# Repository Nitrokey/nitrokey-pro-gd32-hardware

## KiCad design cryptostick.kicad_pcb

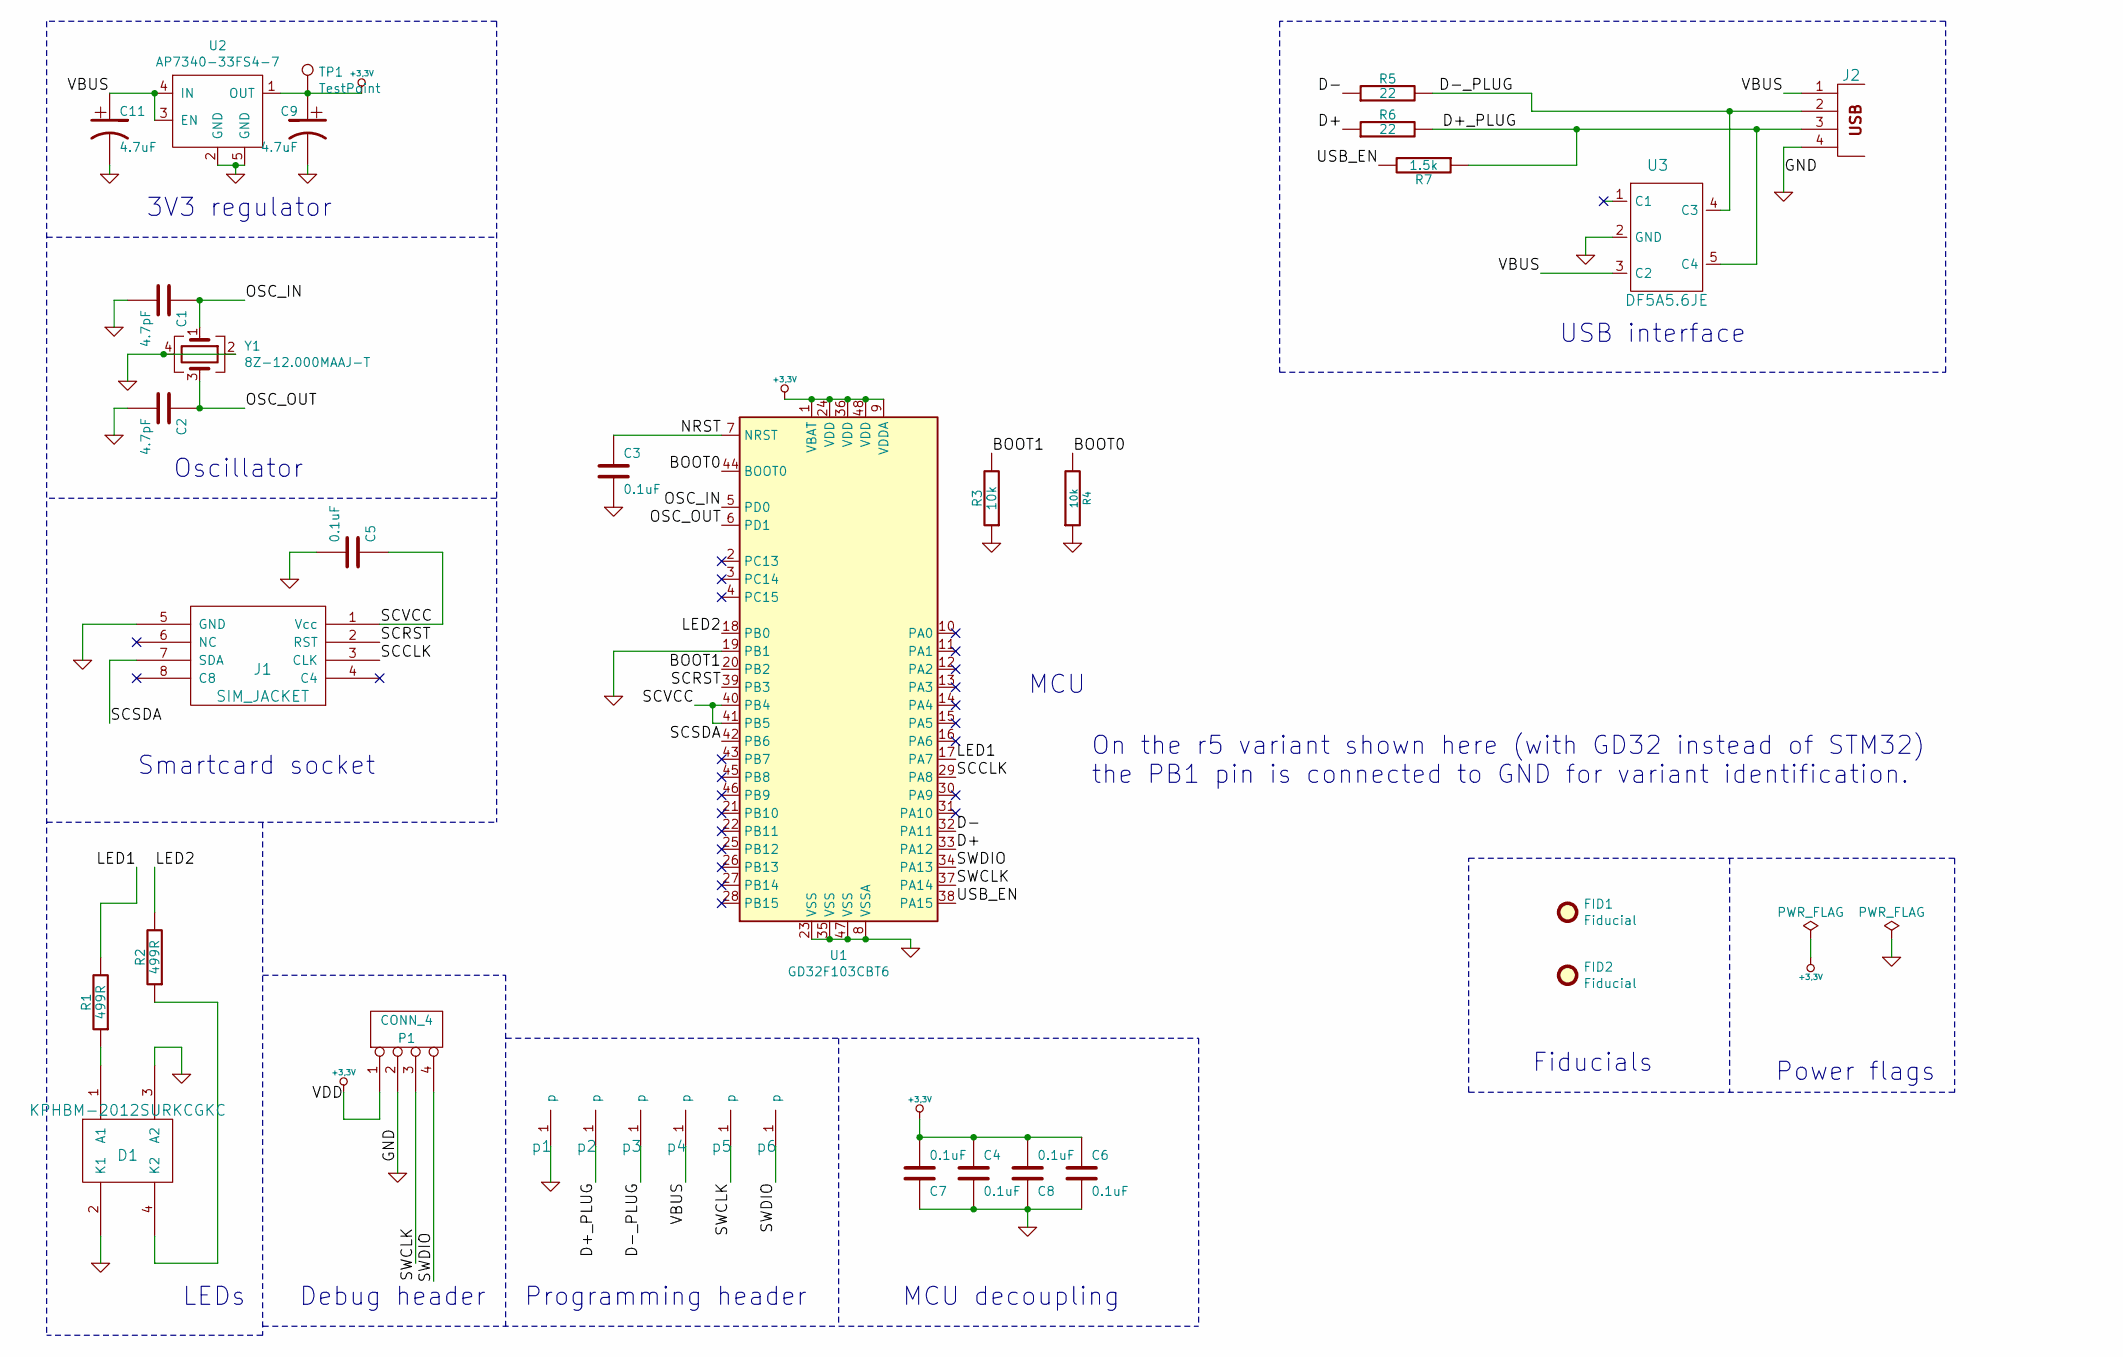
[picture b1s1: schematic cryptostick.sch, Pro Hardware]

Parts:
C1, C2: 4.7pF; C_0402_1005Metric
C3, C4, C5, C6, C7, C8: 0.1uF; C_0402_1005Metric
C9, C11: 4.7uF; C_0402_1005Metric
D1: KPHBM-2012SURKCGKC
FID1, FID2: Fiducial; Fiducial_0.75mm_Mask1.5mm
J1: SIM_JACKET; molex 78646-3001
J2: USB_A; USB-A-PLUG
P1: CONN_4; SIL-2-2-drilled-offset
R1, R2: 499R; R_0402_1005Metric
R3, R4: 10k; R_0402_1005Metric
R5, R6: 22; R_0402_1005Metric
R7: 1.5k; R_0402_1005Metric
TP1: TestPoint; TestPoint_Pad_D1.5mm
U1: GD32F103CBT6; LQFP-48_7x7mm_P0.5mm
U2: AP7340-33FS4-7; Texas_X2SON-4_1x1mm_P0.65mm; MPN TLV74233PDQNR
U3: DF5A5.6JE; SOT-553
Y1: 8Z-12.000MAAJ-T; Crystal_SMD_2520-4Pin_2.5x2.0mm
p1, p2, p3, p5, p6: debug-pin; Prog_Pad_Circular
p4: PROG_VCC; Prog_Pad_Circular

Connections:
+3.3V: C4.1, C6.1, C7.2, C8.2, C9.1, P1.1, TP1.1, U1.1 (VBAT), U1.9 (VDDA), U1.24 (VDD), U1.36 (VDD), U1.48 (VDD), U2.1 (OUT)
/BOOT0: R4.2, U1.44 (BOOT0)
/BOOT1: R3.2, U1.20 (PB2)
/D+: R6.1, U1.33 (PA12)
/D+_PLUG: J2.3, R6.2, R7.1, U3.5 (C4), p2.1
/D-: R5.1, U1.32 (PA11)
/D-_PLUG: J2.2, R5.2, U3.4 (C3), p3.1
/LED1: R1.2, U1.17 (PA7)
/LED2: R2.2, U1.18 (PB0)
/NRST: C3.1, U1.7 (NRST)
/OSC_IN: C1.1, U1.5 (PD0), Y1.1
/OSC_OUT: C2.1, U1.6 (PD1), Y1.3
/SCCLK: J1.3 (CLK), U1.29 (PA8)
/SCRST: J1.2 (RST), U1.39 (PB3)
/SCSDA: J1.7 (SDA), U1.42 (PB6)
/SCVCC: C5.1, J1.1 (Vcc), U1.40 (PB4), U1.41 (PB5)
/SWCLK: P1.3, U1.37 (PA14), p5.1
/SWDIO: P1.4, U1.34 (PA13), p6.1
/USB_EN: R7.2, U1.38 (PA15)
/VBUS: C11.1, J2.1, U2.3 (EN), U2.4 (IN), U3.3 (C2), p4.1
unnamed: D1.1 (A1), R1.1
unnamed: D1.4 (K2), R2.1

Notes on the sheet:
MCU decoupling
Programming header
Debug header
LEDs
Smartcard socket
Oscillator
3V3 regulator
USB interface
MCU
Fiducials
Power flags
On the r5 variant shown here (with GD32 instead of STM32) the PB1 pin is connected to GND for variant identification.

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
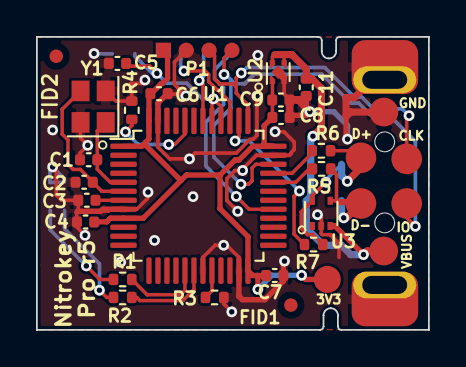
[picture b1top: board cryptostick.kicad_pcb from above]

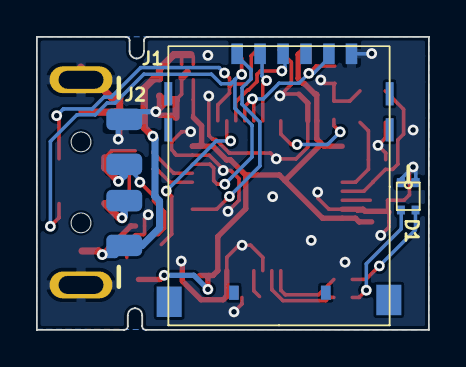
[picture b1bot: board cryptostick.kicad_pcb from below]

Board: 2 copper layers, 21.8 x 16.3 mm, 34 parts (3 on the bottom side), 23 nets.

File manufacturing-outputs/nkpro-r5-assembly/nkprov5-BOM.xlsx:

Id | Designator | Package | Quantity | Designation | Digikey Part Number | Digikey URL | Availability
1 | C3,C7,C6,C5,C4,C8 | c_0402 | 6 | 0.1uF | 20% tol | https://www.digikey.com/en/products/detail/kyocera-avx/0402Z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
2 | R1,R2 | r_0402 | 2 | 499R | 1% tol | https://www.digikey.com/en/products/detail/yageo/RC0402FR-07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
3 | C1,C2 | c_0402 | 2 | 4.7pF | 10% tol | https://www.digikey.com/en/products/detail/murata-electronic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
4 | C9,C11 | c_0402 | 2 | 4.7uF | 20% tol | https://www.digikey.com/en/products/detail/murata-electronic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
5 | U2 | X2SON | 1 | AP7340-33FS4-7 | AP7340-33FS4-7DITR-ND | https://www.digikey.de/product-detail/de/diodes-incorporated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 | 90000
6 | U1 | LQFP48 | 1 | GD32F103CBT6 | winsource GD32F103CBT6 | https://www.win-source.net/hot-sales-and-eol-components-gd32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 | 8600
7 | X1 | Xtal-4-2520-metric | 1 | 8Z-12.000MAAJ-T | 887-1487-2-ND | https://www.digikey.de/product-detail/en/txc-corporation/8Z-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 | 18000
8 | R3,R4 | c_0402 | 2 | 10k | 1% tol | https://www.digikey.com/en/products/detail/samsung-electro-m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
9 | U3 | SOT-553 | 1 | DF5A5.6JE | DF5A5.6CJE,LM | https://www.digikey.de/product-detail/de/toshiba-semiconduct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 | 40000
10 | J2 | USB-A-PLUG | 1 | USB_A | WM3983TR-ND | https://www.digikey.de/product-detail/de/molex/0480372200/WM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 | 26000
11 | D1 | KPHBM-2012SURKCGKC | 1 | DUAL_LED | 754-1093-2-ND | https://www.digikey.de/product-detail/de/kingbright/APHBM201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 | 330000
12 | J1 | Molex 0786463001 | 1 | SIM_JACKET | WM9364CT-ND | http://www.digikey.com/product-detail/en/0786463001/WM9364CT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 | 235000
13 | R7 | r_0402 | 1 | 1.5k | 311-1.50KLRCT-ND | https://www.digikey.com/product-detail/en/yageo/RC0402FR-071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
14 | R5,R6 | r_0402 | 2 | 22R | 311-22.0LRCT-ND | https://www.digikey.com/product-detail/en/yageo/RC0402FR-072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

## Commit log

2021-12-06 r5 with gd32 - separate repository due to major hardware changes
